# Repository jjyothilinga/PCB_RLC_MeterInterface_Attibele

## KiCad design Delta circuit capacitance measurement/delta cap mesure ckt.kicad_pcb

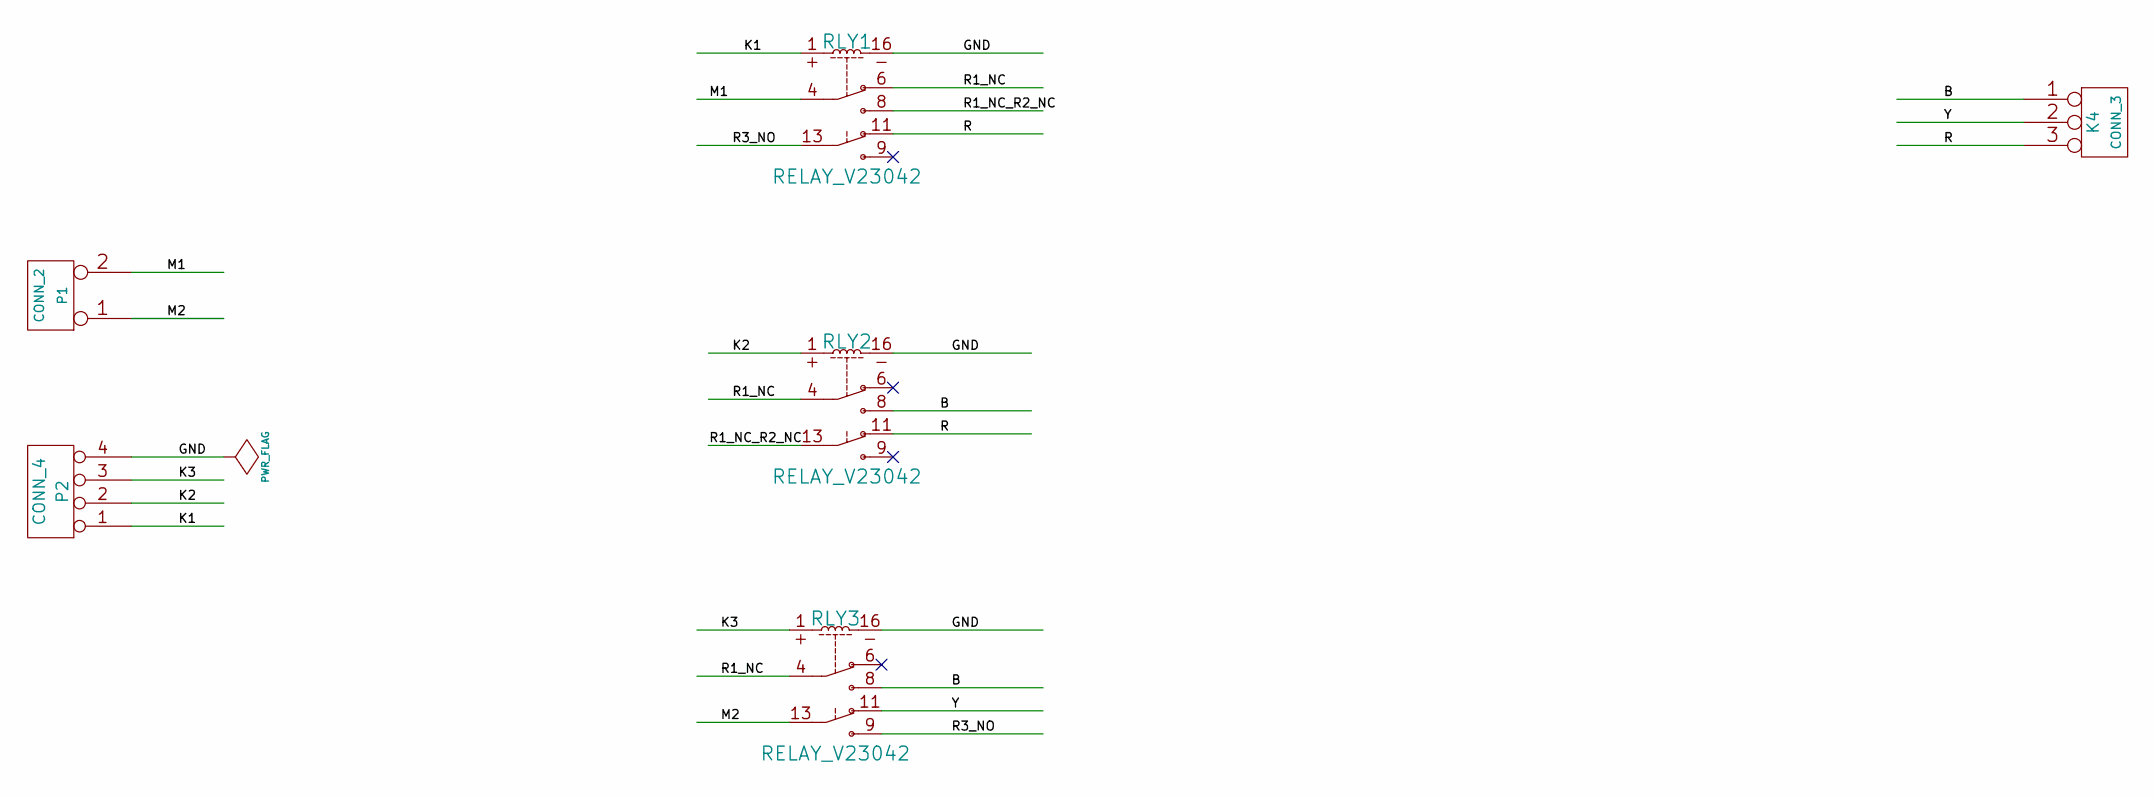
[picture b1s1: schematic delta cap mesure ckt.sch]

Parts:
K4: CONN_3
P1: CONN_2
P2: CONN_4
RLY1, RLY2, RLY3: RELAY_V23042

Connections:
/B: K4.1, RLY2.8, RLY3.8
/GND: P2.4, RLY1.16, RLY2.16, RLY3.16
/K1: P2.1, RLY1.1
/K2: P2.2, RLY2.1
/K3: P2.3, RLY3.1
/M1: P1.2 (PM), RLY1.4
/M2: P1.1, RLY3.13
/R: K4.3, RLY1.11, RLY2.11
/R1_NC: RLY1.6, RLY2.4, RLY3.4
/R1_NC_R2_NC: RLY1.8, RLY2.13
/R3_NO: RLY1.13, RLY3.9
/Y: K4.2 (PM), RLY3.11

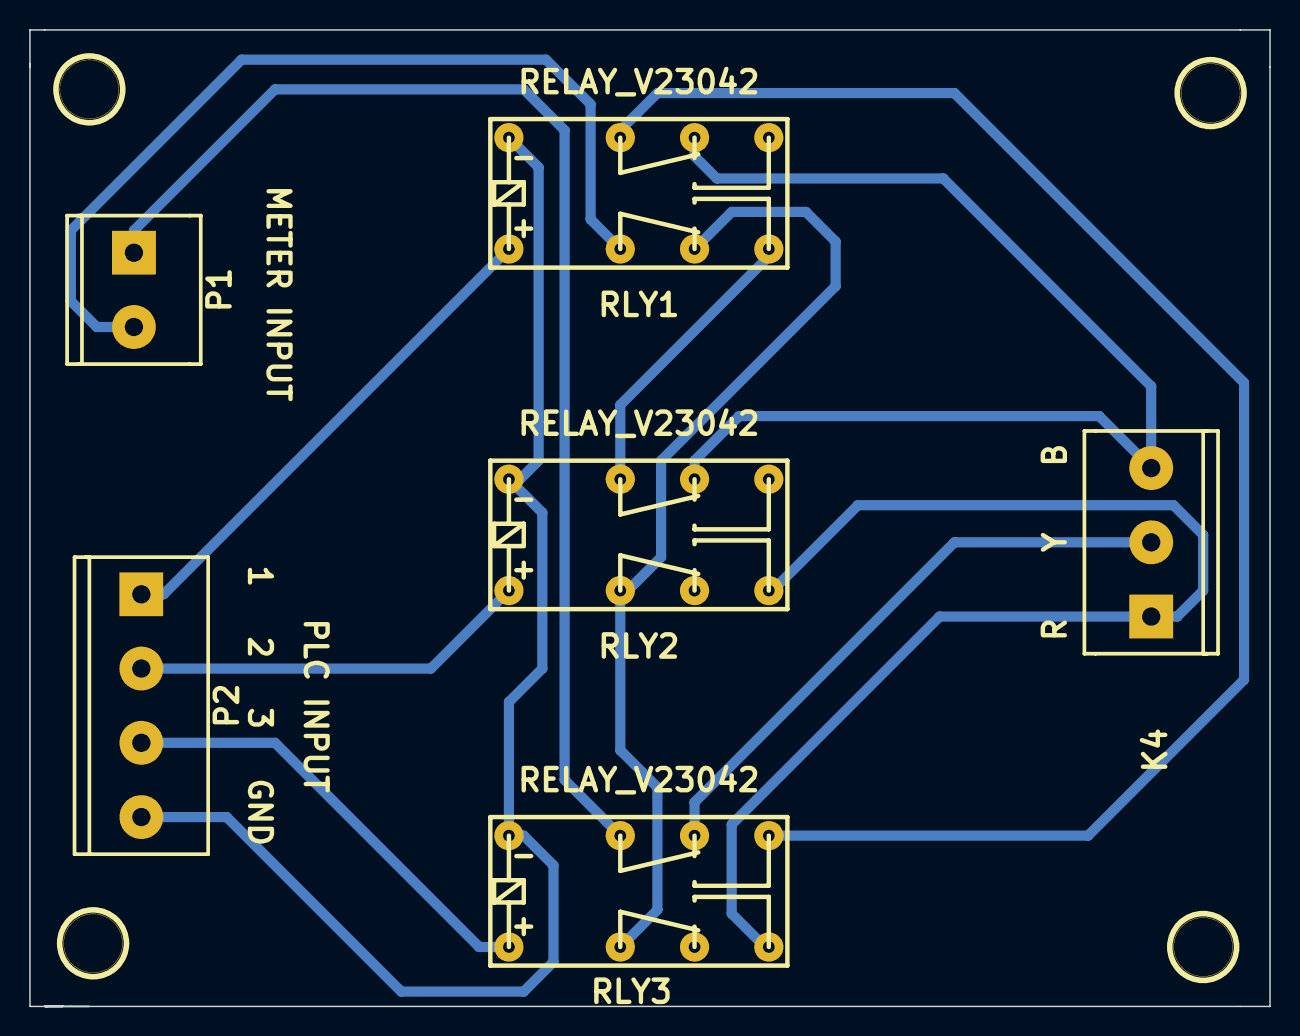
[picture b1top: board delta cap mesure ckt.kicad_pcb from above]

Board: 2 copper layers, 84.8 x 66.8 mm, 10 parts (0 on the bottom side), 12 nets.

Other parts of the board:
1PIN, 1PIN#2, 1PIN#3, 1PIN#4: P***; 1pin

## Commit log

2015-04-17 :tada: Added .gitattributes & .gitignore files
2015-04-17 Completed
2015-05-06 Track width increased
